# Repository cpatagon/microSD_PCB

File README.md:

# Diseño de Circuito Impreso para Conexión con microSD

## Trabajo Práctico Final - Diseño de Circuitos Impresos (DCI)

Este repositorio contiene el trabajo práctico final para la asignatura de Diseño de Circuitos Impresos, parte de la carrera de posgrado en FIUBA.

**Autor:** Luis Gómez  
**Título del Trabajo:** Diseño de Circuito Impreso para Conexión con microSD  
**Descripción:** El proyecto consiste en diseñar una PCB para un conector microSD utilizando KiCad. El objetivo es desarrollar un esquema que incorpore el conector microSD con la correcta asignación de pines para alimentación y comunicación. Posteriormente, se optimizará el diseño de la PCB para asegurar un trazado eficiente de las señales. Finalmente, se generarán los archivos Gerber necesarios para la fabricación de la PCB, fomentando habilidades en el diseño y preparación de circuitos impresos para la producción.

## Licencia

Este trabajo se encuentra bajo la licencia de hardware abierto. GNU GENERAL PUBLIC LICENSE Version 3, 29 June 2007

## Estructura del Trabajo Práctico Final

* **doc**: Información propia sobre el circuito, incluyendo:
  * [documentación del proyecto](./doc/README.md)
  * [documentación propuesta](./doc/propuesta/README.md)

* **info**: Información recopilada de fuentes externas, como:
  * [información de fuentes externas](./info/README.md)

* **pcb**: Archivos de diseño esquemático y de la PCB.
  * [readme diseño PCB](./pcb/README.md)
  * [PCB Checklist](./pcb/Checklist/README.md)

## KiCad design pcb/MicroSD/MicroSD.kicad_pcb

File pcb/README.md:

# Proyecto MicroSD: Adaptador PCB

## 1. Información del Proyecto
- **Nombre del diseñador:** Luis Gómez
- **Email:** lgomez@patagones.cl
- **Nombre del proyecto:** PCB microSD
- **Repositorio:** [https://github.com/cese-dci/tpf24a-cpatagon](https://github.com/cese-dci/tpf24a-cpatagon)
- **Revisión realizada por:** Luis Gómez
- **Fecha de la revisión:** 9/10/2024
- **Fecha último commit:** Wed Oct 9 19:16:56 2024 -0300
- **Curso CESE - PCB:** DCI24A

## 2. Resumen Ejecutivo
Este proyecto consiste en el diseño de un adaptador PCB para tarjetas MicroSD, destinado a facilitar la integración de almacenamiento externo en sistemas embebidos. El diseño se enfoca en la compatibilidad con interfaces de 3.3V y 5V, utilizando componentes SMD para minimizar el tamaño y mejorar el rendimiento.

## 3. Especificaciones Técnicas del PCB

| Característica | Valor |
|----------------|-------|
| Cantidad de capas | 2 |
| Terminación superficial | HASL con Plomo |
| Disposición de componentes | Un lado |
| Tecnología de componentes | SMD |
| Serigrafía | 1 cara |
| Grillas utilizadas | 0,5 mm, 0,25 mm, 0,1 mm |
| Anchos de pistas | 0,35 mm y 0,5 mm |
| Vías/agujeros | 0,7 mm / 0,3 mm |
| Clearance (DRC default) | Sin errores |
| Fabricante | [PCB Chile](https://pcb-chile.cl/) |

## 4. Componentes Principales

### 4.1 Integrado 74LVC125A
- **Función:** Buffer cuádruple de tres estados con entradas tolerantes a 5V.
- **Aplicación:** Adaptación de niveles lógicos y aislamiento de señales.
- **Diagrama:**

  *Figura 1: Diagrama lógico 74LVC125A*

- **Huella:**

  *Figura 2: Huella del integrado 74LVC125A*

### 4.2 Regulador AMS1117
- **Función:** Regulador de voltaje lineal de baja caída.
- **Especificaciones:** Hasta 1A de corriente de salida, comúnmente usado para regular 5V a 3.3V.
- **Diagrama:**

  *Figura 3: Diagrama lógico del regulador AMS1117*

- **Huella:**

  *Figura 4: Huella del regulador AMS1117*

### 4.3 Conector MicroSD
- **Función:** Interfaz física para la tarjeta MicroSD.
- **Diagrama:**

  *Figura 5: Diagrama del conector MicroSD*

- **Huella:**

  *Figura 6: Huella del conector MicroSD*

## 5. Diseño del PCB

### 5.1 Esquemático General
  
*Figura 7: Esquemático general de la PCB MicroSD*

Para más detalles, consulte el [PDF del esquemático completo](PDF/MicroSD.pdf).

### 5.2 Vista General del PCB
  
*Figura 8: Vista general de la PCB para MicroSD*

### 5.3 Huellas de Componentes en PCB
  
*Figura 9: Gerber general con las principales huellas de la PCB*

## 6. Modelos 3D

### 6.1 Vista General 3D
  
*Figura 10: Vista general del modelo 3D de la PCB MicroSD*

### 6.2 Vista Frontal 3D
  
*Figura 11: Vista frontal del modelo 3D con huellas de componentes*

### 6.3 Vista Trasera 3D
  
*Figura 12: Vista trasera del modelo 3D*

## 7. Archivos del Proyecto

### 7.1 Archivos Gerber
Los archivos Gerber necesarios para la fabricación se encuentran en la [carpeta Gerber](Gerber).

### 7.2 Archivos de PCB
Los archivos de diseño de PCB se encuentran en la [carpeta PCB](MicroSD).

- [Archivo PCB Kicad](MicroSD/MicroSD.kicad_pcb)
- [Archivo Esquematico (sch) Kicad](MicroSD/MicroSD.kicad_sch)

#### Estructura del directorio

```
└── MicroSD
    ├── MicroSD.kicad_pcb (PCB)
    ├── MicroSD.kicad_prl
    ├── MicroSD.kicad_pro
    ├── MicroSD.kicad_sch (Esquematico)
    └── sym-lib-table
```

### 7.3 Bibliotecas de Símbolos y Huellas
Las bibliotecas personalizadas utilizadas en este proyecto se encuentran en la [carpeta Libreria](Libreria).

## 8. Consideraciones de Diseño
- Se utilizó un enfoque de ruteo de dos capas para optimizar el espacio y reducir la interferencia electromagnética.
- Se implementaron planos de tierra en ambas capas para mejorar el manejo de EMI.
- Se calculo el ancho mínimo de cada pista de acuerdo a la norma IPC 2221. Se calculo fue hecho con una corriente máxima de 1A, aumento de la temperatura de 10°C y longitud máxima de pista de 100 mm. El ancho de pista resultante fue de 0,3 mm y un grosor de 1 oz de Cu. 

## 9. Próximos Pasos
- Fabricación de prototipos para pruebas y validación.
- Realización de pruebas de funcionamiento a diferentes voltajes (3.3V y 5V).
- Análisis térmico bajo carga máxima.
- Consideración de mejoras para futuras versiones, como la integración de un controlador USB o soporte para velocidades UHS-I.
- Las pistas de datos se diseñaran con impedancia controlada para mantener la integridad de la señal en altas velocidades.

## 10. Conclusiones
Este diseño de PCB para adaptador MicroSD ofrece una solución compacta y versátil para la integración de almacenamiento externo en sistemas embebidos, con consideraciones especiales para la compatibilidad de voltajes y el rendimiento de alta velocidad.

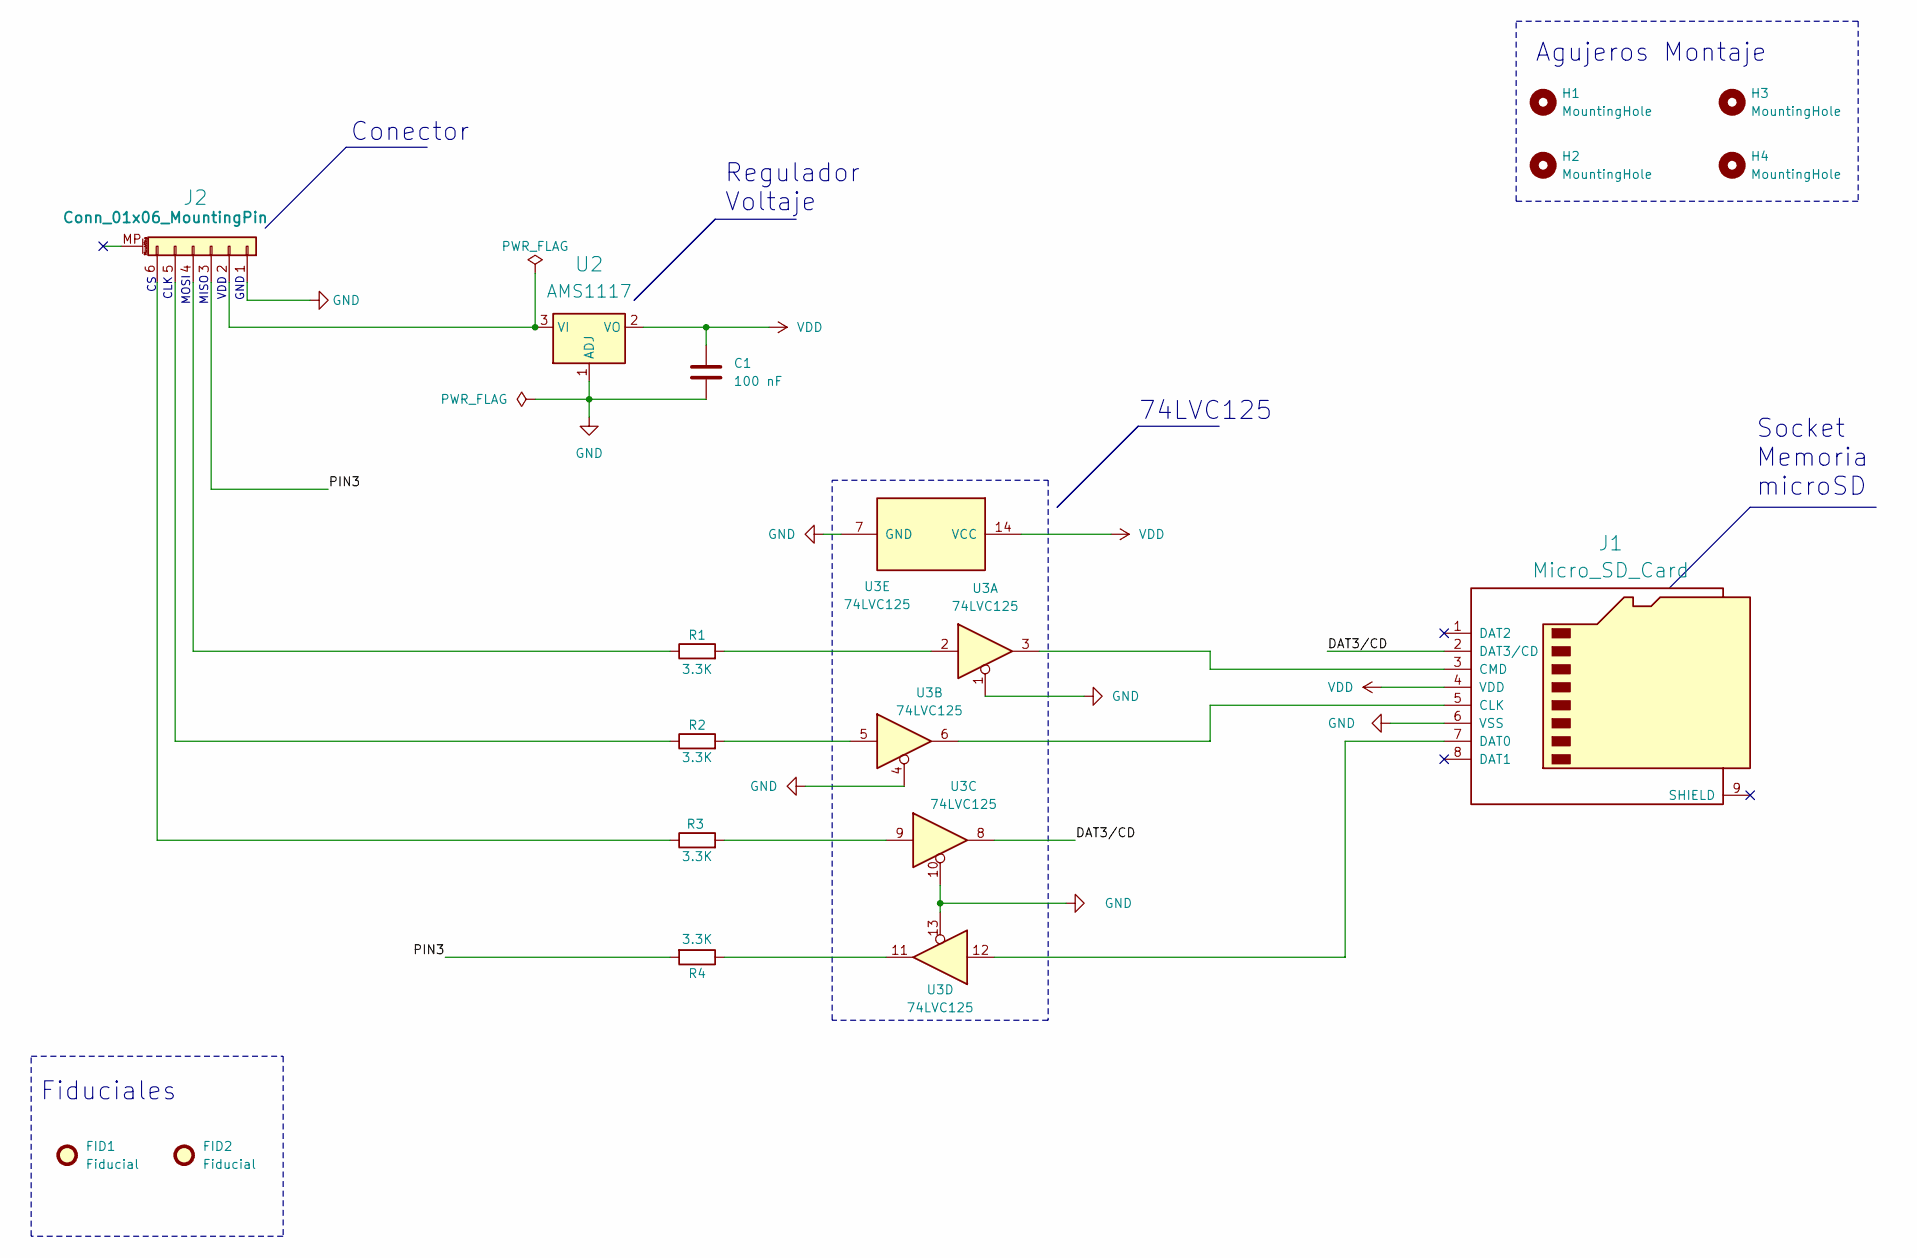
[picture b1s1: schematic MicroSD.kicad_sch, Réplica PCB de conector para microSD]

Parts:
C1: 100 nF; C_1206_3216Metric_Pad1.33x1.80mm_HandSolder
FID1, FID2: Fiducial; Fiducial_1.5mm_Mask3mm
H1, H2, H3, H4: MountingHole; MountingHole_2mm
J1: Micro_SD_Card; microSD_HC_Hirose_DM3D-SF
J2: Conn_01x06_MountingPin; Molex_PicoBlade_53398-0671_1x06-1MP_P1.25mm_Vertical
R1, R2, R3, R4: 3.3K; R_0603_1608Metric
U2: AMS1117; SOT-223-3_TabPin2
U3: 74LVC125; DIP-14_W7.62mm_SMDSocket_SmallPads

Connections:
/DAT3/CD: J1.2 (DAT3/CD), U3.8
/PIN3: J2.3, R4.2
GND: C1.2, J1.6 (VSS), J2.1, U2.1 (ADJ), U3.1, U3.4, U3.7 (GND), U3.10, U3.13
unnamed: J1.5 (CLK), U3.6
unnamed: J1.3 (CMD), U3.3
unnamed: J1.7 (DAT0), U3.12
unnamed: J2.2, U2.3 (VI)
unnamed: J2.4, R1.1
unnamed: J2.5, R2.1
unnamed: J2.6, R3.1
unnamed: R1.2, U3.2
unnamed: R2.2, U3.5
unnamed: R3.2, U3.9
unnamed: R4.1, U3.11
VDD: C1.1, J1.4 (VDD), U2.2 (VO), U3.14 (VCC)

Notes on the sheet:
VDD
CLK
MISO
Fiduciales
Conector
MOSI
GND
Socket Memoria microSD
74LVC125
Agujeros Montaje
Regulador Voltaje

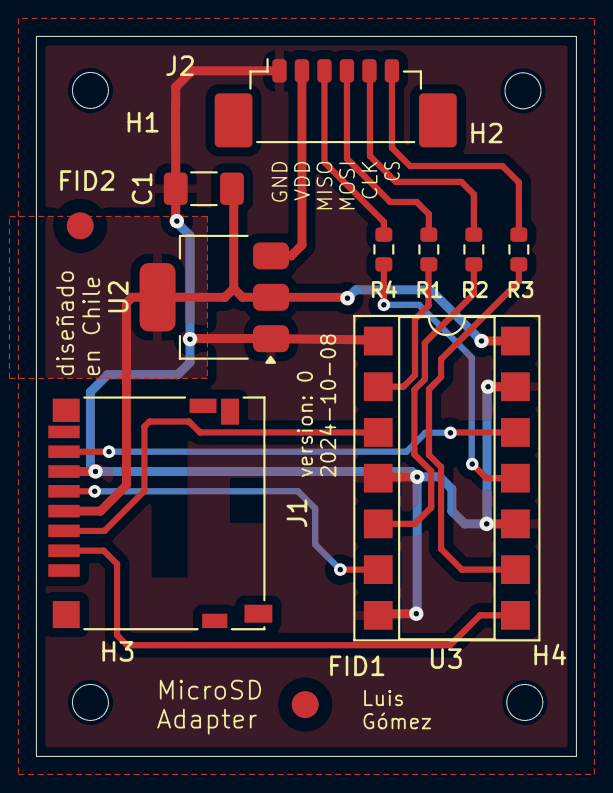
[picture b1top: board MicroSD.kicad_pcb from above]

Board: 2 copper layers, 30.0 x 40.0 mm, 15 parts (0 on the bottom side), 15 nets.

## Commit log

2024-09-02 se actualiza readme
2024-09-02 se actualiza propuesta
2024-09-02 se agrega esquemático
2024-09-02 se gregan archivos proyecto
2024-09-15 actualizacion esquematico
2024-09-16 se actualizan README
2024-09-16 se actualizan README 2
2024-09-16 se actualizan README 3
2024-09-16 se actualizan README 4
2024-09-16 se actualizan README 5
2024-09-16 se actualizan README 6
2024-09-25 se agrega PCB
2024-09-25 se agrega PCB 2
2024-09-26 se agregan agujeros montaje
2024-10-08 se actualiza PCB y esquemas
2024-10-08 se actualiza PCB y esquemas 2
2024-10-09 se actualiza resultados
2024-10-09 se agregan figuras y gerber
2024-10-09 se actualiza README 2
2024-10-09 se actualiza README 4
2024-10-09 se actualiza README 5
2024-10-09 se README
2024-10-10 README doc
2024-10-10 se README 5
2024-10-10 se README 6
2024-10-10 README doc 2
2024-10-10 README doc 3
2024-10-10 README doc 4
2024-10-10 se README 7
2024-10-10 se README 8
2024-10-10 se README 9
2024-10-10 se README 10
2024-10-10 se README 11
2024-10-10 se README 12
2024-10-10 se README 13
2024-10-10 README doc 15
2024-10-10 se modifica readme
2024-10-10 se README 18
2024-10-10 se README 19
2024-10-10 README doc 16
2024-10-10 README doc 17
2024-10-10 README doc 18
2024-10-10 se README 20
2024-10-10 se cambia tamaño
2024-10-11 se eliminan error del pcb

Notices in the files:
pcb/MicroSD/MicroSD.kicad_pcb:
Licencia: GNU GENERAL PUBLIC LICENSE Version 3, 29 June 2007
